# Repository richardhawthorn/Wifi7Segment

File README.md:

### Features

- 0.56" 7 segment display, 4 character
- ESP8266 ESP7/12/12E Processor
- Wifi connected
- HT16K33 i2c LED driver
- 3.3V operation
- Mini USB power connector
- FTDI programming port
- Through hole technology

### License

This work is licensed under a Creative Commons Attribution-ShareAlike 4.0 International License.

<br />
Designed by <a xmlns:cc="http://creativecommons.org/ns#" href="http://www.richardhawthorn.com" property="cc:attributionName" rel="cc:attributionURL" target="_blank">Richard Hawthorn</a><br />
<a rel="license" href="http://creativecommons.org/licenses/by-sa/4.0/" target="_blank">View License</a>

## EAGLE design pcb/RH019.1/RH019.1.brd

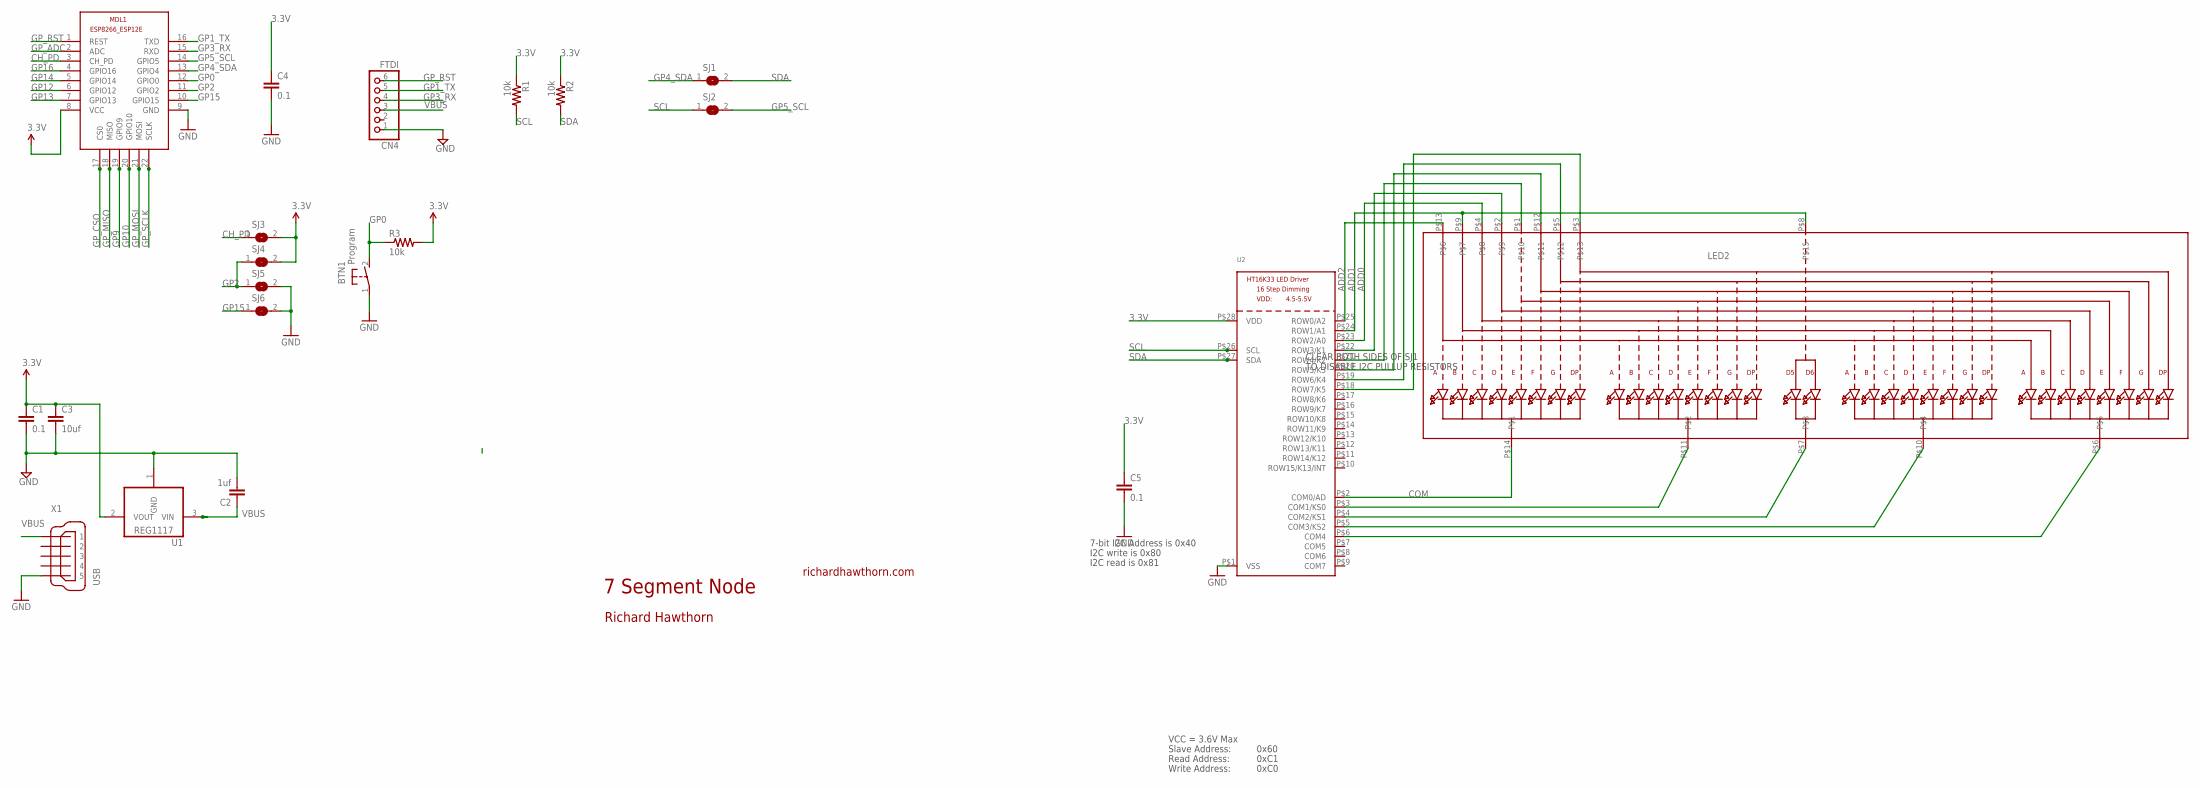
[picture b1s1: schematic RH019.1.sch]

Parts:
BTN1: Program; DTS-3
C1, C4, C5: 0.1; CAP-PTH-SMALL2
C2: 1uf; CAP-PTH-SMALL2
C3: 10uf; CAP-PTH-SMALL2
CN4: FTDI; 1X06
LED2: DISP_SEGMENT_4DIGIT_BL-Q56C43; SEGMENT-BL-Q56C43
MDL1: ESP8266-12EESP8266-ESP12E; ESP8266-ESP12E
R1, R2, R3: 10k; 0204/7
SJ1, SJ2, SJ3, SJ4, SJ5, SJ6: SJ
U1: REG1117; SOT223
U2: HT16K33_SOP28; SOP28_300MIL
X1: USB; 32005-601

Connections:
3.3V: C1.1, C3.1, C4.1, C5.1, MDL1.8 (VCC), R1.1, R2.1, R3.2, SJ3.2, SJ4.2, U1.2 (VOUT), U2.P$28 (VDD)
ADD0: LED2.P$4, U2.P$23 (ROW2/A0)
ADD1: LED2.P$8, LED2.P$9, U2.P$24 (ROW1/A1)
ADD2: LED2.P$13, U2.P$25 (ROW0/A2)
CH_PD: MDL1.3 (CH_PD), SJ3.1
COM: LED2.P$14, U2.P$2 (COM0/AD)
GND: BTN1.1, C1.2, C2.2, C3.2, C4.2, C5.2, CN4.1, MDL1.9 (GND), SJ5.2, SJ6.2, U1.1 (GND), U2.P$1 (VSS), X1.5
GP0: BTN1.2, MDL1.12 (GPIO0), R3.1
GP1_TX: CN4.5, MDL1.16 (TXD)
GP2: MDL1.11 (GPIO2), SJ4.1, SJ5.1
GP3_RX: CN4.4, MDL1.15 (RXD)
GP4_SDA: MDL1.13 (GPIO4), SJ1.1
GP5_SCL: MDL1.14 (GPIO5), SJ2.2
GP9: MDL1.19 (GPIO9)
GP10: MDL1.20 (GPIO10)
GP12: MDL1.6 (GPIO12)
GP13: MDL1.7 (GPIO13)
GP14: MDL1.5 (GPIO14)
GP15: MDL1.10 (GPIO15), SJ6.1
GP16: MDL1.4 (GPIO16)
GP_ADC: MDL1.2 (ADC)
GP_CSO: MDL1.17 (CS0)
GP_MISO: MDL1.18 (MISO)
GP_MOSI: MDL1.21 (MOSI)
GP_RST: CN4.6, MDL1.1 (REST)
GP_SCLK: MDL1.22 (SCLK)
unnamed: LED2.P$11, U2.P$3 (COM1/KS0)
unnamed: LED2.P$7, U2.P$4 (COM2/KS1)
unnamed: LED2.P$10, U2.P$5 (COM3/KS2)
unnamed: LED2.P$6, U2.P$6 (COM4)
unnamed: LED2.P$2, U2.P$22 (ROW3/K1)
unnamed: LED2.P$1, U2.P$21 (ROW4/K2)
unnamed: LED2.P$12, U2.P$20 (ROW5/K3)
unnamed: LED2.P$5, U2.P$19 (ROW6/K4)
unnamed: LED2.P$3, U2.P$18 (ROW7/K5)
SCL: R1.2, SJ2.1, U2.P$26 (SCL)
SDA: R2.2, SJ1.2, U2.P$27 (SDA)
VBUS: C2.1, CN4.3, U1.3 (VIN), X1.1

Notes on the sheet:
7 Segment Node
richardhawthorn.com
Richard Hawthorn
CLEAR BOTH SIDES OF SJ1
TO DISABLE I2C PULLUP RESISTORS
7-bit I2C Address is 0x40
I2C write is 0x80
I2C read is 0x81
VCC = 3.6V Max
Read Address:
Write Address:
Slave Address:
0x60
0xC1
0xC0

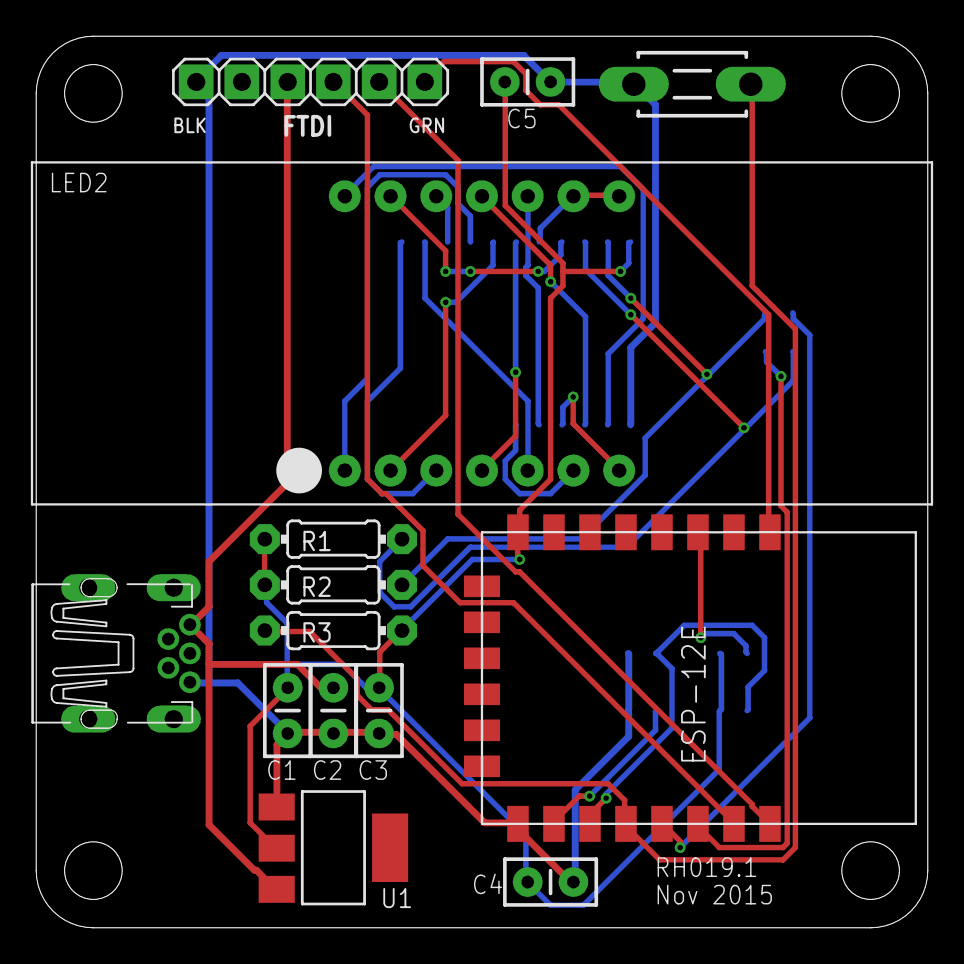
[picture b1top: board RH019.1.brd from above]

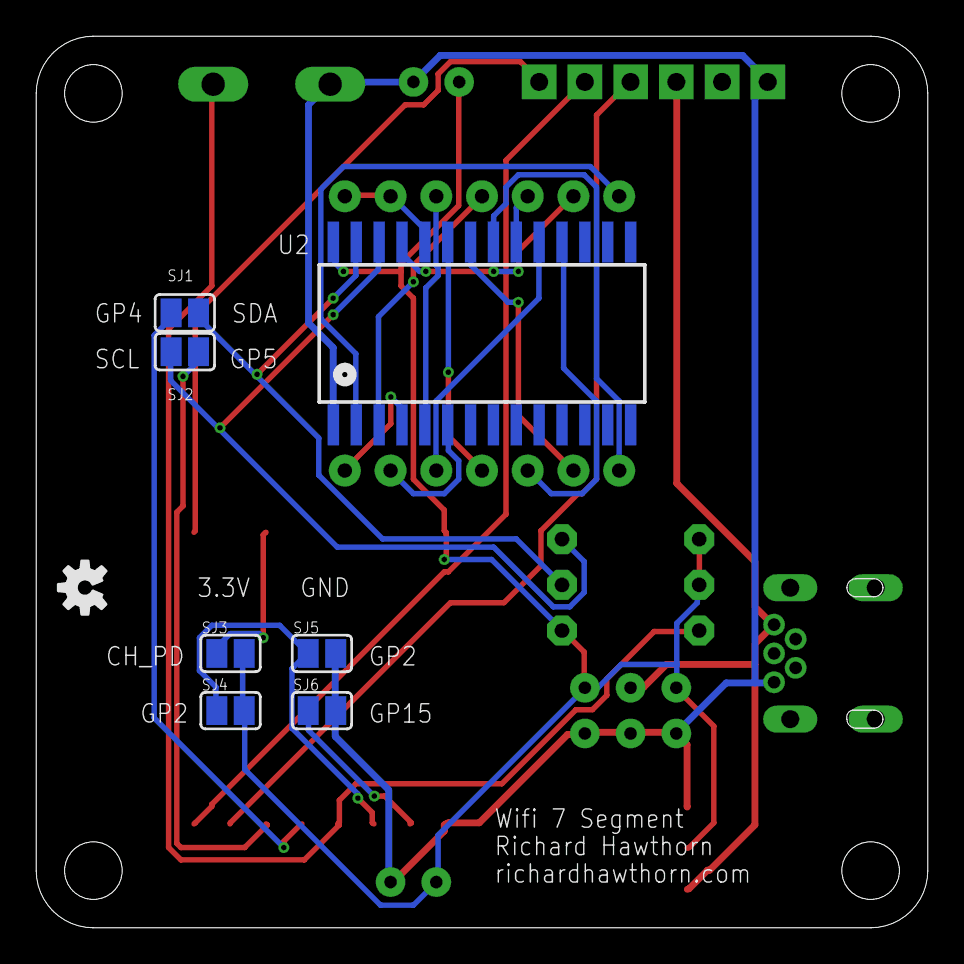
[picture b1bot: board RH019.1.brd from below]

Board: 2 copper layers, 49.5 x 49.5 mm, 22 parts (8 on the bottom side), 27 nets.

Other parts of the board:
U$3: OSHW-LOGO-S

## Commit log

2015-11-10 First version added
2015-11-10 added gerbers
2015-11-10 added images
2015-12-01 updated pcb and gerbers
2016-01-03 add images
2016-01-03 update gitignore
2016-01-03 add readme
2016-11-08 added bom

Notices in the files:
parts and their libraries:
SparkFun-Aesthetics: Licensing: CC v3.0 Share-Alike You are welcome to use this library for commercial purposes.
